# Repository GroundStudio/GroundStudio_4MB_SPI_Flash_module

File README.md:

GroundStudio Flash 32 module
====================================

Get it from [ardushop.ro](https://ardushop.ro/ro/home/1849-modul-memorie-flash-32bit-4mbyte.html)

Explore all the GroundStudio products at [GroundStudio.ro](https://groundstudio.ro/)

Description
-------------------
32Mb/4MB SPI flash memory module based on W25Q32 chip.

Contents
-------------------

* [/Documentation](https://github.com/GroundStudio/GroundStudio_4MB_SPI_Flash_module/tree/main/Documentation) -- Contains documentation written during creation of this repository, with readme.md index of its own!
* [/Firmware](https://github.com/GroundStudio/GroundStudio_4MB_SPI_Flash_module/tree/main/Firmware) -- Firmware (bootloaders, etc)
* [/Hardware](https://github.com/GroundStudio/GroundStudio_4MB_SPI_Flash_module/tree/main/Hardware) -- Schematics, layout.
* [/Libraries](https://github.com/GroundStudio/GroundStudio_4MB_SPI_Flash_module/tree/main/Libraries) -- Arduino/CircuitPython libraries. 
* [/Tools](https://github.com/GroundStudio/GroundStudio_4MB_SPI_Flash_module/tree/main) -- Tools needed for compiling, uploading bootloader, etc.

Versions
-------------------
*(Not all tags shown)*
* [V0.1] Initial version

License
-------------------

This is released under the [Attribution-ShareAlike 4.0 International (CC BY-SA 4.0)](https://creativecommons.org/licenses/by-sa/4.0/) license. 
**You are welcome to use this for commercial purposes.**

Please consider contributing back to this project or others to help the open-source hardware community continue to thrive and grow! 

Certifications:

[Open Source Hardware Association](https://certification.oshwa.org/ro000021.html)   
   
[
](https://certification.oshwa.org/ro000021.html)

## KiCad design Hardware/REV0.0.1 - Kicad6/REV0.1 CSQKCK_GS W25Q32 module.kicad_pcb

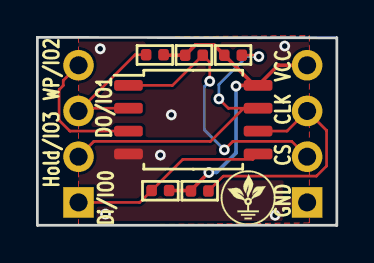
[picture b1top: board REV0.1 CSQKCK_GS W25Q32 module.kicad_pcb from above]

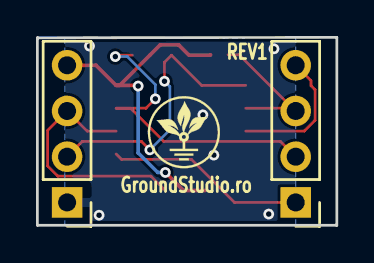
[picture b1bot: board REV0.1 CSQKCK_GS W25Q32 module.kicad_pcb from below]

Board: 2 copper layers, 16.6 x 10.4 mm, 8 parts (2 on the bottom side), 8 nets.

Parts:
J1, J2: Conn_01x04; PinHeader_1x04_P2.54mm_Vertical_Male
R1, R2, R3, R4, R5: 10k; R_0402_1005Metric
U1: W25Q64JVSSIQ; SOIC-8_5.275x5.275mm_P1.27mm

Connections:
CLK: J2.3, R1.2, U1.6
CS: J2.2, R2.2, U1.1
DI_IO0: J1.1, R3.2, U1.5
DO_IO1: J1.3, R5.2, U1.2
GND: J2.1, U1.4
HOLD_IO3: J1.2, R4.2, U1.7
VCC: J2.4, R1.1, R2.1, R3.1, R4.1, R5.1, U1.8
WP_IO2: J1.4, U1.3

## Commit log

2023-10-24 - first commit
2023-10-25 - added datasheet
